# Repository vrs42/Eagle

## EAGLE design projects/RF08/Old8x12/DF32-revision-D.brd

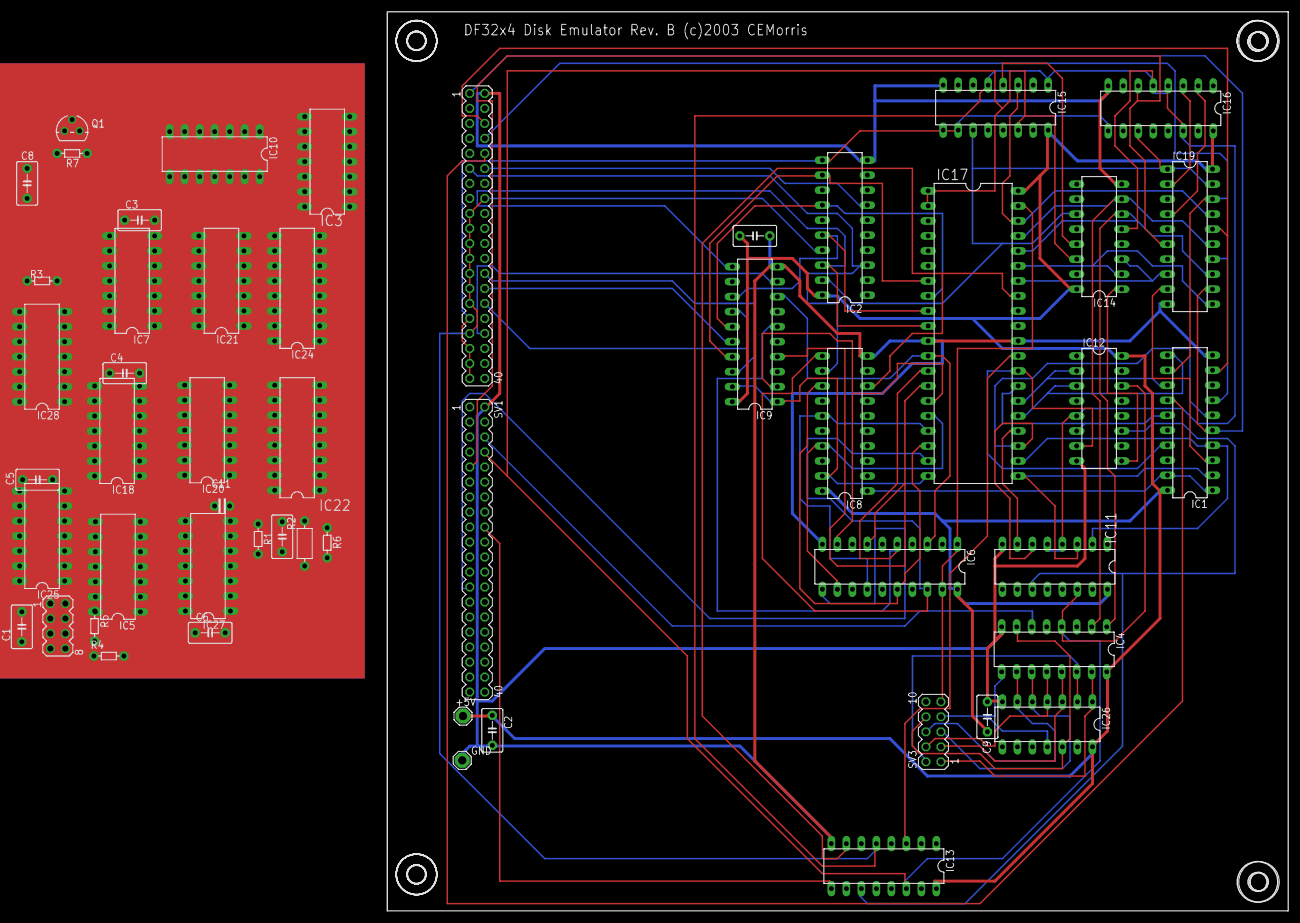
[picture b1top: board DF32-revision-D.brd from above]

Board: 2 copper layers, 152.5 x 152.2 mm, 56 parts (0 on the bottom side), 153 nets.

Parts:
+5V: SE14
C1, C2, C3, C4, C5, C6, C7, C8, C9, C10: C5B3.5
C11: C-2,5
GND: SE14
IC1, IC8, IC9, IC19: 74LS240N; DIL20
IC2, IC6: 74LS244N; DIL20
IC3: 74LS00N; DIL14
IC4: 74LS138N; DIL16
IC5: 74LS32N; DIL14
IC7, IC18, IC25: 74LS74N; DIL14
IC10: 74LS04N; DIL14
IC11, IC12, IC13, IC14, IC15, IC16: 74LS191N; DIL16
IC17: DS1258; DIL40
IC20: 74LS02N; DIL14
IC21: 74LS01N; DIL14
IC22, IC24: 74LS155N; DIL16
IC26: 74LS30N; DIL14
IC27: 74LS86N; DIL14
IC28: 74LS07N; DIL14
Q1: 2N3904; TO92
R1: 1K; R-5
R2: 1K; R-7,5
R3, R4, R5: 220; R-5
R6: 0; R-5
R7: 4.7K; R-5
SV1: BUS1; MA20-2
SV2: BUS2; MA20-2
SV3: WRLOCK; MA05-2
SV4: PANEL LEDS; MA04-2
U$1, U$2, U$3, U$4: 3,0

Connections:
0V: IC2.17, IC7.2, IC7.12, IC11.4, IC11.5, IC12.5, IC13.5, IC14.5, IC15.1, IC15.5, IC16.4, IC16.5, IC16.14, R6.1, SV2.16, SV2.17, SV2.19, SV2.21, SV2.23, SV2.25, SV2.27, SV2.29, SV2.33
!660-663: IC5.8, IC22.2, IC24.2, IC24.14
!(NED+EWL): IC2.13, IC20.1
!ACBUS0: IC2.3, IC8.12, SV2.11
!ACBUS1: IC8.14, IC19.3, SV2.9
!ACBUS2: IC8.16, IC19.5, SV2.7
!ACBUS3: IC8.18, IC19.7, SV2.5
!ACBUS4: IC1.3, IC19.9, SV2.3
!ACBUS5: IC1.5, IC19.12, SV2.1
!ACBUS6: IC1.7, IC19.14, SV2.4
!ACBUS7: IC1.9, IC19.16, SV2.6
!ACBUS8: IC1.12, IC19.18, SV2.8
!ACBUS9: IC1.14, IC2.5, SV2.10
!ACBUS10: IC1.16, IC2.7, SV2.12
!ACBUS11: IC1.18, IC2.9, SV2.14
!ACCLEAR: IC21.1, IC28.4, IC28.6, IC28.8, IC28.12, SV1.1
!BADDAC: IC7.3, SV1.10
!BBREAK: IC4.4, IC10.13, IC11.14, IC12.14, IC13.14, IC14.14, IC15.14, IC17.1, IC17.2, SV1.8
!BRK_RQ: IC7.8, SV2.15
!BWCO: IC7.11, IC18.3, SV1.12
!DATA0: IC8.9, SV2.18
!DATA1: IC8.7, SV2.20
!DATA2: IC8.5, SV2.22
!DATA3: IC8.3, SV2.24
!DATA4: IC9.18, SV2.26
!DATA5: IC9.16, SV2.28
!DATA6: IC9.14, SV2.30
!DATA7: IC9.12, SV2.32
!DATA8: IC9.9, SV2.34
!DATA9: IC9.7, SV2.36
!DATA10: IC9.5, SV2.38
!DATA11: IC9.3, SV2.40
!DRL: IC2.15, IC7.6
!EA: IC10.10, SV1.4
!EWL: IC18.8, IC28.11
!INT_RQ: IC21.13, SV1.16
!IOP4: IC10.4, IC24.15
!IOS: IC21.4, IC21.10, IC28.2, SV1.14
!IOT601: IC22.7, IC27.12
!IOT602: IC3.12, IC24.7, IC25.3, IC28.3
!IOT604: IC3.13, IC7.4, IC24.9, IC25.1, IC28.9
!IOT612: IC24.6, IC28.1, IC28.5, IC28.13
!IOT614: IC2.19, IC14.11, IC15.11, IC16.11, IC19.1, IC19.19, IC24.10
!IOT621: IC10.5, IC22.5
!IOT622: IC10.9, IC20.11, IC24.5
!IOT624: IC1.1, IC1.19, IC8.1, IC24.11
!LAD: IC3.8, IC7.10, IC11.11, IC12.11, IC13.11
!OE: IC3.6, IC8.19, IC9.1, IC9.19, IC17.20
!SCL: IC7.1, IC7.13, IC18.1, IC18.13, IC20.10, IC25.13
!WE: IC2.1, IC6.1, IC6.19, IC17.39, IC27.9, R2.2, SV3.9
!WR1: IC4.15, IC26.1, SV3.1
!WR2: IC4.14, IC26.2, SV3.2
!WR3: IC4.13, IC26.3, SV3.3
!WR4: IC4.12, IC26.4, SV3.4
!WR5: IC4.11, IC26.5, SV3.5
!WR6: IC4.10, IC26.6, SV3.6
!WR7: IC4.9, IC26.11, SV3.7
!WR8: IC4.7, IC26.12, SV3.8
BAC0: IC13.9, SV1.18
BAC1: IC13.10, IC15.15, SV1.20
BAC2: IC13.1, IC14.9, SV1.22
BAC3: IC13.15, IC14.10, SV1.24
BAC4: IC12.9, IC14.1, SV1.26
BAC5: IC12.10, IC14.15, SV1.28
BAC6: IC12.1, IC16.10, SV1.30
BAC7: IC12.15, IC16.1, SV1.32
BAC8: IC11.9, IC16.15, SV1.34
BAC9: IC11.10, SV1.36
BAC10: IC11.1, SV1.38
BAC11: IC11.15, SV1.40
BIOP1: IC22.1, SV1.11
BIOP2: IC24.1, SV1.13
BIOP4: IC10.3, SV1.15
BMB0: IC6.2, SV1.17
BMB1: IC6.4, SV1.19
BMB2: IC6.6, SV1.21
BMB3: IC3.1, IC6.8, SV1.23
BMB4: IC3.2, IC6.11, SV1.25
BMB5: IC5.12, IC6.13, SV1.27
BMB6: IC5.13, IC6.15, SV1.29
BMB7: IC6.17, IC22.3, IC24.3, SV1.31
BMB8: IC2.2, IC22.13, IC24.13, SV1.33
BMB9: IC2.4, IC20.12, IC21.3, SV1.35
BMB10: IC2.6, SV1.37
BMB11: IC2.8, SV1.39
BRK_RQ: IC7.9, R7.2
BTS3: IC4.6, SV1.6
DATA_IN: IC3.4, IC4.5, IC25.5, SV2.13
DISK_LED: R4.1, SV4.3
DMA0: IC8.8, IC13.7, IC17.33
DMA1: IC8.6, IC13.6, IC17.32
DMA2: IC8.4, IC13.2, IC17.31
DMA3: IC8.2, IC13.3, IC17.29
DMA4: IC1.17, IC12.7, IC17.28
DMA5: IC1.15, IC12.6, IC17.27
DMA6: IC1.13, IC12.2, IC17.26
DMA7: IC1.11, IC12.3, IC17.25
DMA8: IC1.8, IC11.7, IC17.24
DMA9: IC1.6, IC11.6, IC17.23
DMA10: IC1.4, IC11.2, IC17.22
DMA11: IC1.2, IC11.3, IC17.21
DQ0: IC6.18, IC8.11, IC17.19
DQ1: IC6.16, IC8.13, IC17.18
DQ2: IC6.14, IC8.15, IC17.17
DQ3: IC6.12, IC8.17, IC17.16
DQ4: IC6.9, IC9.2, IC17.15
DQ5: IC6.7, IC9.4, IC17.14
DQ6: IC6.5, IC9.6, IC17.13
DQ7: IC6.3, IC9.8, IC17.12
DQ8: IC2.18, IC9.11, IC17.10
DQ9: IC2.16, IC9.13, IC17.9
DQ10: IC2.14, IC9.15, IC17.8
DQ11: IC2.12, IC9.17, IC17.7
DRL: IC5.2, IC7.5
EA1: IC10.11, IC16.3, IC19.2, SV1.5
EA2: IC16.2, IC19.4, SV1.7
EA3: IC16.6, IC19.6, SV1.9
EMA1: IC14.3, IC17.34, IC19.8
EMA2: IC14.2, IC17.35, IC19.11
EMA3: IC4.1, IC14.6, IC17.36, IC19.13
EMA4: IC4.2, IC14.7, IC17.37, IC19.15
EMA5: IC4.3, IC15.3, IC17.38, IC19.17
EWL: IC5.1, IC18.9, IC20.2
EWLSET: IC18.11, IC27.6
GND: C1.2, C2.2, C3.2, C4.2, C5.2, C6.2, C7.2, C8.2, C9.2, C10.2, C11.2, GND.MP, IC1.10, IC2.10, IC3.7, IC4.8, IC5.7, IC6.10, IC7.7, IC8.10, IC9.10, IC10.7, IC11.8, IC12.8, IC13.8, IC14.8, IC15.8, IC16.8, IC17.11, IC17.30, IC18.7, IC19.10, IC20.7, IC21.7, IC22.8, IC24.8, IC25.7, IC26.7, IC27.7, IC28.7, Q1.3, R6.2, SV1.2, SV2.2, SV4.5, SV4.7
IOT601: IC20.9, IC27.11
IOT621: IC10.6, IC21.9
LAD: IC3.9, IC3.10, IC3.11
unnamed: C11.1, IC27.5, IC27.8
unnamed: IC5.6, IC21.11, IC21.12
unnamed: IC28.10, R3.2
unnamed: IC3.5, IC10.12
unnamed: Q1.1, R4.2
unnamed: R5.2, SV4.6
unnamed: IC13.13, IC14.4
unnamed: IC12.13, IC13.4
unnamed: IC11.13, IC12.4
unnamed: IC3.3, IC5.9
unnamed: IC14.13, IC15.4
unnamed: IC5.10, IC5.11
unnamed: IC20.13, IC21.5
unnamed: IC5.3, IC20.5
unnamed: IC10.8, IC21.2
unnamed: IC26.8, IC27.4
unnamed: Q1.2, R7.1
NED: IC5.4, IC20.3, IC20.6, IC25.9
NEDSET: IC15.2, IC25.11
NOERR: IC20.4, IC21.8
PWRCLR: IC20.8, IC25.4, SV1.3
TRC: IC5.5, IC18.5, IC21.6
V+: IC2.11, IC15.9, IC15.10, IC16.9, IC18.2, IC18.4, IC18.10, IC18.12, IC22.14, IC22.15, IC25.2, IC25.10, IC25.12, IC27.1, IC27.2, IC27.10, IC27.13, R1.1, R2.1, SV2.31, SV2.35, SV2.37, SV2.39
VCC: +5V.MP, C1.1, C2.1, C3.1, C4.1, C5.1, C6.1, C7.1, C8.1, C9.1, C10.1, IC1.20, IC2.20, IC3.14, IC4.16, IC5.14, IC6.20, IC7.14, IC8.20, IC9.20, IC10.14, IC11.16, IC12.16, IC13.16, IC14.16, IC15.16, IC16.16, IC17.40, IC18.14, IC19.20, IC20.14, IC21.14, IC22.16, IC24.16, IC25.14, IC26.14, IC27.14, IC28.14, R1.2, R5.1, SV4.2, SV4.4, SV4.8
WRITELOCK_LED: R3.1, SV4.1

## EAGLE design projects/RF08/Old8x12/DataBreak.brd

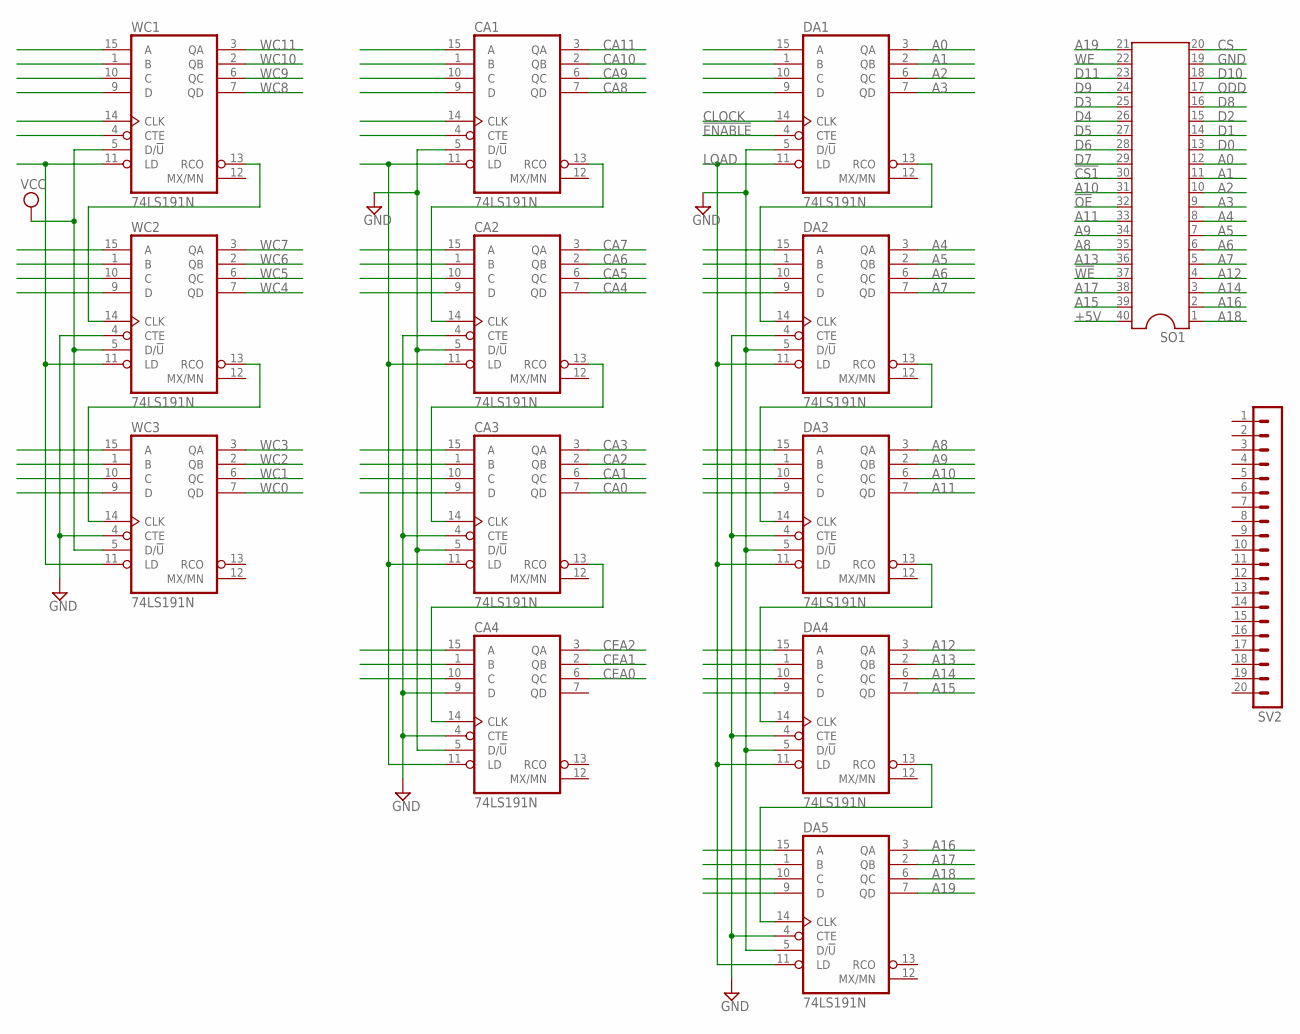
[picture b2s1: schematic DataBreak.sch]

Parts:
CA1, CA2, CA3, CA4: 74LS191N; DIL16
DA1, DA2, DA3, DA4, DA5: 74LS191N; DIL16
SO1: DIL40
SV2: MA20-1L
WC1, WC2, WC3: 74LS191N; DIL16

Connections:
!CS1: SO1.30
!ENABLE: DA1.4 (CTE)
!OE: SO1.32
!WE: SO1.37
+5V: SO1.40
A0: DA1.3 (QA), SO1.12
A1: DA1.2 (QB), SO1.11
A2: DA1.6 (QC), SO1.10
A3: DA1.7 (QD), SO1.9
A4: DA2.3 (QA), SO1.8
A5: DA2.2 (QB), SO1.7
A6: DA2.6 (QC), SO1.6
A7: DA2.7 (QD), SO1.5
A8: DA3.3 (QA), SO1.35
A9: DA3.2 (QB), SO1.34
A10: DA3.6 (QC), SO1.31
A11: DA3.7 (QD), SO1.33
A12: DA4.3 (QA), SO1.4
A13: DA4.2 (QB), SO1.36
A14: DA4.6 (QC), SO1.3
A15: DA4.7 (QD), SO1.39
A16: DA5.3 (QA), SO1.2
A17: DA5.2 (QB), SO1.38
A18: DA5.6 (QC), SO1.1
A19: DA5.7 (QD), SO1.21
CA0: CA3.7 (QD)
CA1: CA3.6 (QC)
CA2: CA3.2 (QB)
CA3: CA3.3 (QA)
CA4: CA2.7 (QD)
CA5: CA2.6 (QC)
CA6: CA2.2 (QB)
CA7: CA2.3 (QA)
CA8: CA1.7 (QD)
CA9: CA1.6 (QC)
CA10: CA1.2 (QB)
CA11: CA1.3 (QA)
CEA0: CA4.6 (QC)
CEA1: CA4.2 (QB)
CEA2: CA4.3 (QA)
CLOCK: DA1.14 (CLK)
CS: SO1.20
D0: SO1.13
D1: SO1.14
D2: SO1.15
D3: SO1.25
D4: SO1.26
D5: SO1.27
D6: SO1.28
D7: SO1.29
D8: SO1.16
D9: SO1.24
D10: SO1.18
D11: SO1.23
GND: CA1.5 (D/!U), CA1.8 (GND), CA2.4 (CTE), CA2.5 (D/!U), CA2.8 (GND), CA3.4 (CTE), CA3.5 (D/!U), CA3.8 (GND), CA4.4 (CTE), CA4.5 (D/!U), CA4.8 (GND), CA4.9 (D), DA1.5 (D/!U), DA1.8 (GND), DA2.4 (CTE), DA2.5 (D/!U), DA2.8 (GND), DA3.4 (CTE), DA3.5 (D/!U), DA3.8 (GND), DA4.4 (CTE), DA4.5 (D/!U), DA4.8 (GND), DA5.4 (CTE), DA5.5 (D/!U), DA5.8 (GND), SO1.19, WC1.8 (GND), WC2.4 (CTE), WC2.8 (GND), WC3.4 (CTE), WC3.8 (GND)
LOAD: DA1.11 (LD), DA2.11 (LD), DA3.11 (LD), DA4.11 (LD), DA5.11 (LD)
unnamed: DA1.13 (RCO), DA2.14 (CLK)
unnamed: DA2.13 (RCO), DA3.14 (CLK)
unnamed: DA3.13 (RCO), DA4.14 (CLK)
unnamed: DA4.13 (RCO), DA5.14 (CLK)
unnamed: WC1.13 (RCO), WC2.14 (CLK)
unnamed: WC2.13 (RCO), WC3.14 (CLK)
unnamed: CA1.13 (RCO), CA2.14 (CLK)
unnamed: CA2.13 (RCO), CA3.14 (CLK)
unnamed: CA3.13 (RCO), CA4.14 (CLK)
unnamed: CA1.11 (LD), CA2.11 (LD), CA3.11 (LD), CA4.11 (LD)
unnamed: WC1.11 (LD), WC2.11 (LD), WC3.11 (LD)
ODD: SO1.17
VCC: CA1.16 (VCC), CA2.16 (VCC), CA3.16 (VCC), CA4.16 (VCC), DA1.16 (VCC), DA2.16 (VCC), DA3.16 (VCC), DA4.16 (VCC), DA5.16 (VCC), WC1.5 (D/!U), WC1.16 (VCC), WC2.5 (D/!U), WC2.16 (VCC), WC3.5 (D/!U), WC3.16 (VCC)
WC0: WC3.7 (QD)
WC1: WC3.6 (QC)
WC2: WC3.2 (QB)
WC3: WC3.3 (QA)
WC4: WC2.7 (QD)
WC5: WC2.6 (QC)
WC6: WC2.2 (QB)
WC7: WC2.3 (QA)
WC8: WC1.7 (QD)
WC9: WC1.6 (QC)
WC10: WC1.2 (QB)
WC11: WC1.3 (QA)
WE: SO1.22

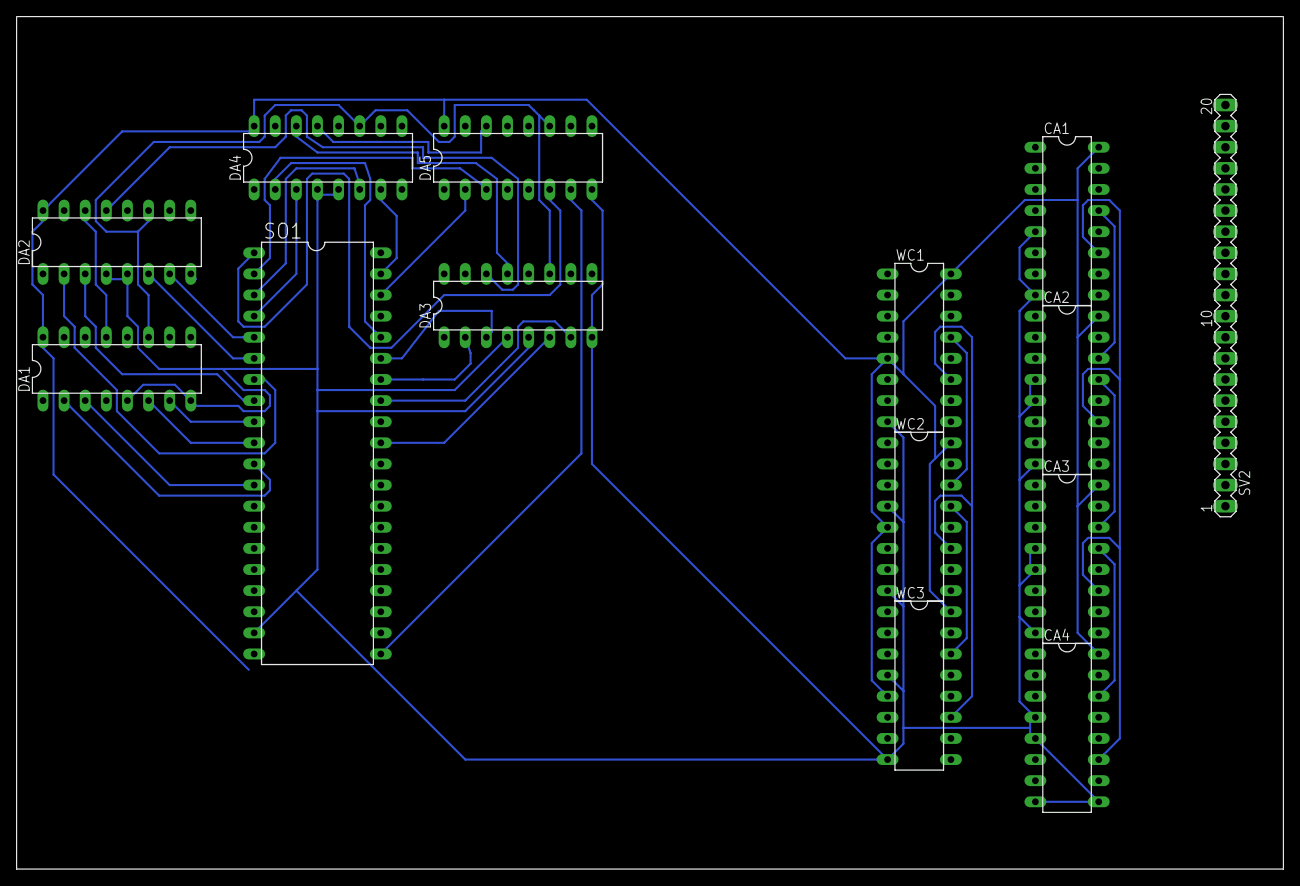
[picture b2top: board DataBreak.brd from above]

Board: 2 copper layers, 152.4 x 102.5 mm, 14 parts (0 on the bottom side), 34 nets.

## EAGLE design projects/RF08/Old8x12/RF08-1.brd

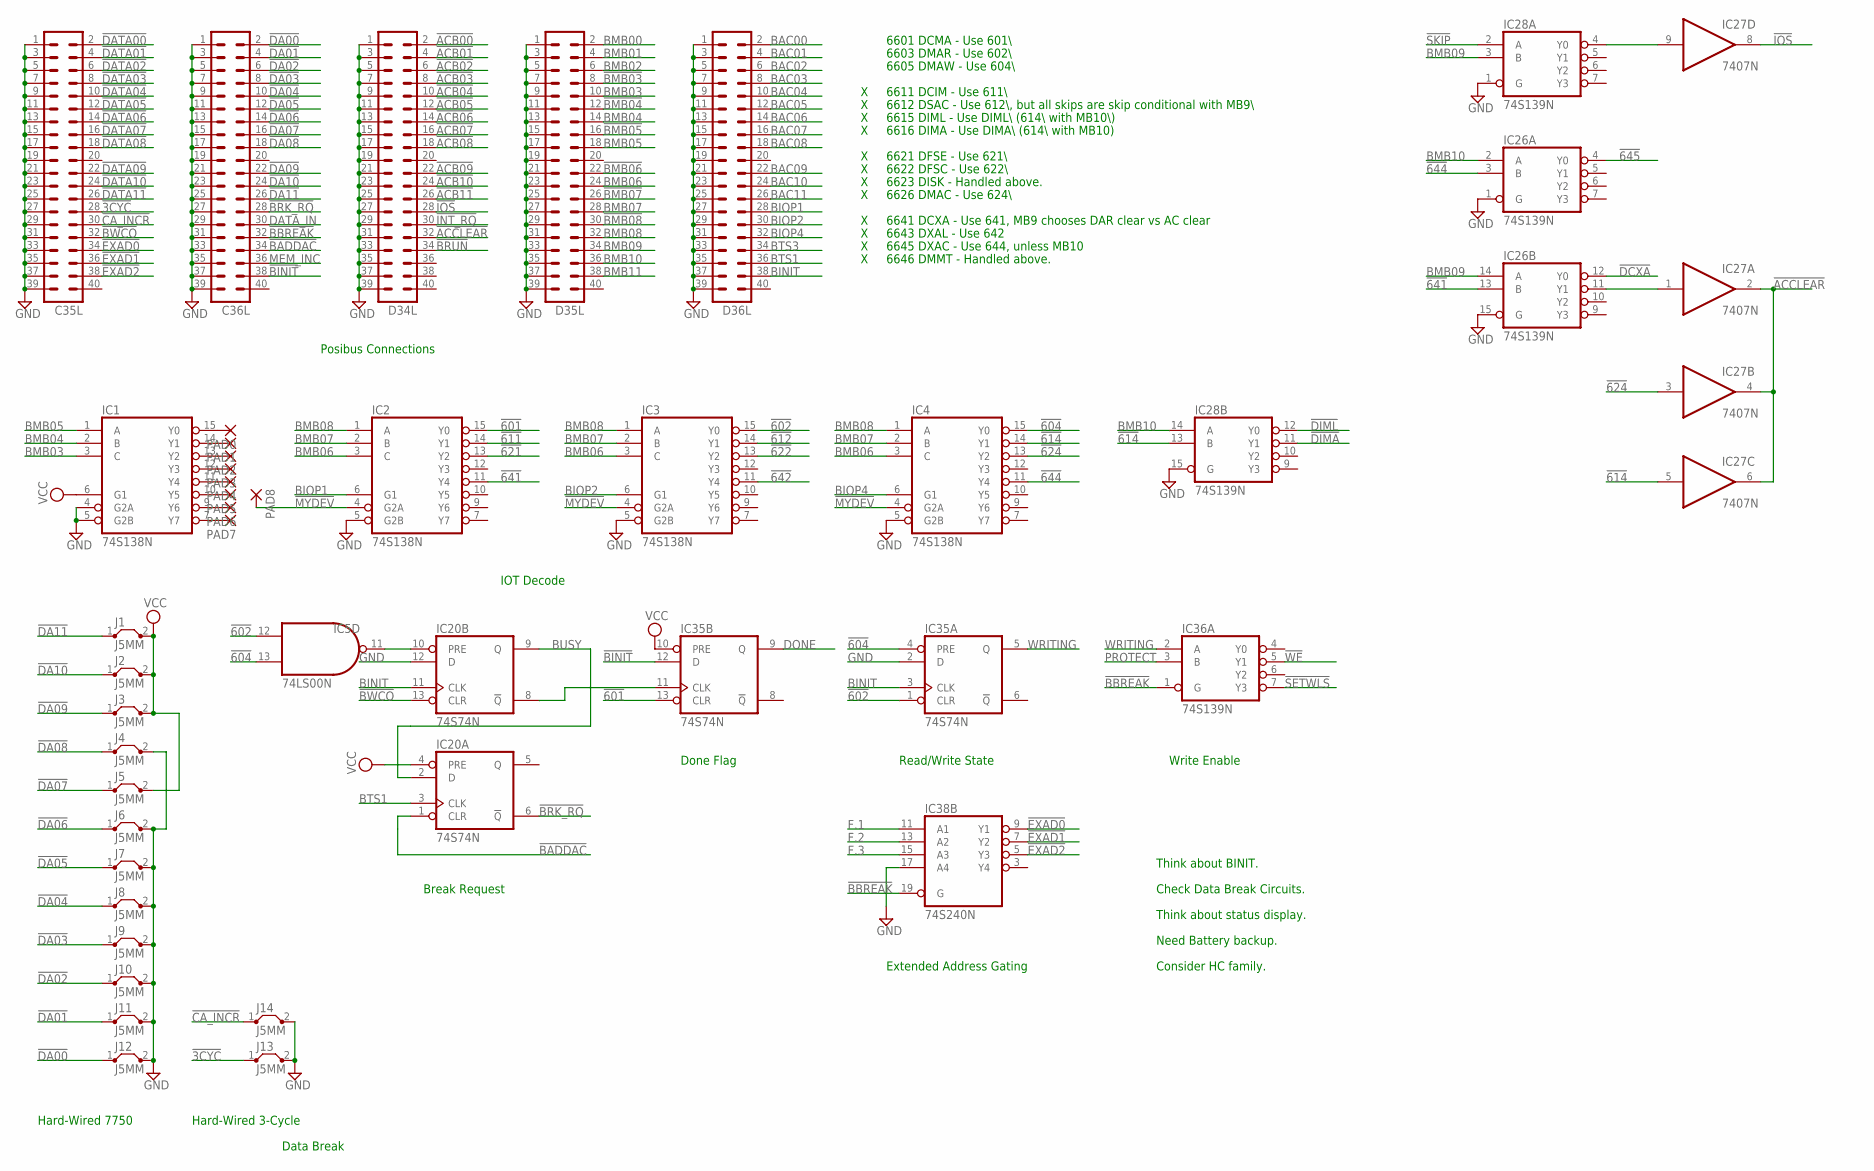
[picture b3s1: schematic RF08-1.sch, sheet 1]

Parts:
C35L, C36L: MA20-2
D34L, D35L, D36L: MA20-2
IC1, IC2, IC3, IC4: 74S138N; DIL16
IC5: 74LS00N; DIL14
IC20, IC35: 74S74N; DIL14
IC26, IC28, IC36: 74S139N; DIL16
IC27: 7407N; DIL14
IC38: 74S240N; DIL20
J1, J2, J3, J4, J5, J6, J7, J8, J9, J10, J11, J12, J13, J14: J5MM; 05
PAD0, PAD1, PAD2, PAD3, PAD4, PAD5, PAD6, PAD7, PAD8: 1,6/0,8

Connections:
!3CYC: C35L.28, J13.1
!601: IC2.15 (Y0), IC35.13 (CLR); also elsewhere on the board
!602: IC3.15 (Y0), IC5.12 (I0), IC35.1 (CLR); also elsewhere on the board
!604: IC4.15 (Y0), IC5.13 (I1), IC35.4 (PRE); also elsewhere on the board
!611: IC2.14 (Y1); also elsewhere on the board
!612: IC3.14 (Y1); also elsewhere on the board
!614: IC4.14 (Y1), IC27.5 (I), IC28.13 (B)
!621: IC2.13 (Y2); also elsewhere on the board
!622: IC3.13 (Y2); also elsewhere on the board
!624: IC4.13 (Y2), IC27.3 (I); also elsewhere on the board
!641: IC2.11 (Y4), IC26.13 (B)
!642: IC3.11 (Y4); also elsewhere on the board
!644: IC4.11 (Y4), IC26.3 (B)
!645: IC26.4 (Y0); also elsewhere on the board
!ACB00: D34L.2; also elsewhere on the board
!ACB01: D34L.4; also elsewhere on the board
!ACB02: D34L.6; also elsewhere on the board
!ACB03: D34L.8; also elsewhere on the board
!ACB04: D34L.10; also elsewhere on the board
!ACB05: D34L.12; also elsewhere on the board
!ACB06: D34L.14; also elsewhere on the board
!ACB07: D34L.16; also elsewhere on the board
!ACB08: D34L.18; also elsewhere on the board
!ACB09: D34L.22; also elsewhere on the board
!ACB10: D34L.24; also elsewhere on the board
!ACB11: D34L.26; also elsewhere on the board
!ACCLEAR: D34L.32, IC27.2 (O), IC27.4 (O), IC27.6 (O)
!BADDAC: C36L.34, IC20.1 (CLR)
!BBREAK: C36L.32, IC36.1 (G), IC38.19 (G); also elsewhere on the board
!BINIT: C36L.38, IC35.12 (D)
!BMB03: D35L.8
!BMB04: D35L.12
!BMB05: D35L.16
!BMB06: D35L.22
!BMB07: D35L.26
!BMB08: D35L.30
!BRK_RQ: C36L.28, IC20.6 (!Q)
!BRUN: D34L.34
!BWCO: C35L.32, IC20.13 (CLR)
!CA_INCR: C35L.30, J14.1
!DA00: C36L.2, J12.1
!DA01: C36L.4, J11.1
!DA02: C36L.6, J10.1
!DA03: C36L.8, J9.1
!DA04: C36L.10, J8.1
!DA05: C36L.12, J7.1
!DA06: C36L.14, J6.1
!DA07: C36L.16, J5.1
!DA08: C36L.18, J4.1
!DA09: C36L.22, J3.1
!DA10: C36L.24, J2.1
!DA11: C36L.26, J1.1
!DATA00: C35L.2; also elsewhere on the board
!DATA01: C35L.4; also elsewhere on the board
!DATA02: C35L.6; also elsewhere on the board
!DATA03: C35L.8; also elsewhere on the board
!DATA04: C35L.10; also elsewhere on the board
!DATA05: C35L.12; also elsewhere on the board
!DATA06: C35L.14; also elsewhere on the board
!DATA07: C35L.16; also elsewhere on the board
!DATA08: C35L.18; also elsewhere on the board
!DATA09: C35L.22; also elsewhere on the board
!DATA10: C35L.24; also elsewhere on the board
!DATA11: C35L.26; also elsewhere on the board
!DCXA: IC26.12 (Y0); also elsewhere on the board
!DIMA: IC28.11 (Y1); also elsewhere on the board
!DIML: IC28.12 (Y0); also elsewhere on the board
!EXAD0: C35L.34, IC38.9 (Y1)
!EXAD1: C35L.36, IC38.7 (Y2)
!EXAD2: C35L.38, IC38.5 (Y3)
!INT_RQ: D34L.30; also elsewhere on the board
!IOS: D34L.28, IC27.8 (O)
!MYDEV: IC2.4 (G2A), IC3.4 (G2A), IC4.4 (G2A), PAD8.1
!SETWLS: IC36.7 (Y3); also elsewhere on the board
!SKIP: IC28.2 (A); also elsewhere on the board
!WE: IC36.5 (Y1); also elsewhere on the board
BAC00: D36L.2; also elsewhere on the board
BAC01: D36L.4; also elsewhere on the board
BAC02: D36L.6; also elsewhere on the board
BAC03: D36L.8; also elsewhere on the board
BAC04: D36L.10; also elsewhere on the board
BAC05: D36L.12; also elsewhere on the board
BAC06: D36L.14; also elsewhere on the board
BAC07: D36L.16; also elsewhere on the board
BAC08: D36L.18; also elsewhere on the board
BAC09: D36L.22; also elsewhere on the board
BAC10: D36L.24; also elsewhere on the board
BAC11: D36L.26; also elsewhere on the board
BINIT: D36L.38, IC20.11 (CLK), IC35.3 (CLK); also elsewhere on the board
BIOP1: D36L.28, IC2.6 (G1)
BIOP2: D36L.30, IC3.6 (G1)
BIOP4: D36L.32, IC4.6 (G1)
BMB00: D35L.2; also elsewhere on the board
BMB01: D35L.4; also elsewhere on the board
BMB02: D35L.6; also elsewhere on the board
BMB03: D35L.10, IC1.3 (C); also elsewhere on the board
BMB04: D35L.14, IC1.2 (B); also elsewhere on the board
BMB05: D35L.18, IC1.1 (A); also elsewhere on the board
BMB06: D35L.24, IC2.3 (C), IC3.3 (C), IC4.3 (C); also elsewhere on the board
BMB07: D35L.28, IC2.2 (B), IC3.2 (B), IC4.2 (B); also elsewhere on the board
BMB08: D35L.32, IC2.1 (A), IC3.1 (A), IC4.1 (A); also elsewhere on the board
BMB09: D35L.34, IC26.14 (A), IC28.3 (B); also elsewhere on the board
BMB10: D35L.36, IC26.2 (A), IC28.14 (A); also elsewhere on the board
BMB11: D35L.38; also elsewhere on the board
BTS1: D36L.36, IC20.3 (CLK)
BTS3: D36L.34
BUSY: IC20.2 (D), IC20.9 (Q); also elsewhere on the board
DATA_IN: C36L.30
DONE: IC35.9 (Q); also elsewhere on the board
F.1: IC38.11 (A1); also elsewhere on the board
F.2: IC38.13 (A2); also elsewhere on the board
F.3: IC38.15 (A3); also elsewhere on the board
GND: C35L.1, C35L.3, C35L.5, C35L.7, C35L.9, C35L.11, C35L.13, C35L.15, C35L.17, C35L.19, C35L.21, C35L.23, C35L.25, C35L.27, C35L.29, C35L.31, C35L.33, C35L.35, C35L.37, C35L.39, C36L.1, C36L.3, C36L.5, C36L.7, C36L.9, C36L.11, C36L.13, C36L.15, C36L.17, C36L.19, C36L.21, C36L.23, C36L.25, C36L.27, C36L.29, C36L.31, C36L.33, C36L.35, C36L.37, C36L.39, D34L.1, D34L.3, D34L.5, D34L.7, D34L.9, D34L.11, D34L.13, D34L.15, D34L.17, D34L.19, D34L.21, D34L.23, D34L.25, D34L.27, D34L.29, D34L.31, D34L.33, D34L.35, D34L.37, D34L.39, D35L.1, D35L.3, D35L.5, D35L.7, D35L.9, D35L.11, D35L.13, D35L.15, D35L.17, D35L.19, D35L.21, D35L.23, D35L.25, D35L.27, D35L.29, D35L.31, D35L.33, D35L.35, D35L.37, D35L.39, D36L.1, D36L.3, D36L.5, D36L.7, D36L.9, D36L.11, D36L.13, D36L.15, D36L.17, D36L.19, D36L.21, D36L.23, D36L.25, D36L.27, D36L.29, D36L.31, D36L.33, D36L.35, D36L.37, D36L.39, IC1.4 (G2A), IC1.5 (G2B), IC1.8 (GND), IC2.5 (G2B), IC2.8 (GND), IC3.5 (G2B), IC3.8 (GND), IC4.5 (G2B), IC4.8 (GND), IC5.7 (GND), IC20.7 (GND), IC20.12 (D), IC26.1 (G), IC26.8 (GND), IC26.15 (G), IC27.7 (GND), IC28.1 (G), IC28.8 (GND), IC28.15 (G), IC35.2 (D), IC35.7 (GND), IC36.8 (GND), IC38.10 (GND), IC38.17 (A4), J4.2, J6.2, J7.2, J8.2, J9.2, J10.2, J11.2, J12.2, J13.2, J14.2; also elsewhere on the board
MEM_INC: C36L.36
unnamed: IC1.9 (Y6), PAD6.1
unnamed: IC20.8 (!Q), IC35.11 (CLK)
unnamed: IC1.15 (Y0), PAD0.1
unnamed: IC1.14 (Y1), PAD1.1
unnamed: IC1.13 (Y2), PAD2.1
unnamed: IC1.12 (Y3), PAD3.1
unnamed: IC1.11 (Y4), PAD4.1
unnamed: IC1.10 (Y5), PAD5.1
unnamed: IC1.7 (Y7), PAD7.1
unnamed: IC26.11 (Y1), IC27.1 (I)
unnamed: IC27.9 (I), IC28.4 (Y0)
unnamed: IC5.11 (O), IC20.10 (PRE)
PROTECT: IC36.3 (B); also elsewhere on the board
VCC: IC1.6 (G1), IC1.16 (VCC), IC2.16 (VCC), IC3.16 (VCC), IC4.16 (VCC), IC5.14 (VCC), IC20.4 (PRE), IC20.14 (VCC), IC26.16 (VCC), IC27.14 (VCC), IC28.16 (VCC), IC35.10 (PRE), IC35.14 (VCC), IC36.16 (VCC), IC38.20 (VCC), J1.2, J2.2, J3.2, J5.2; also elsewhere on the board
WRITING: IC35.5 (Q), IC36.2 (A); also elsewhere on the board

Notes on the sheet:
6601 DCMA - Use 601\\
6603 DMAR - Use 602\\
6605 DMAW - Use 604\\
6611 DCIM - Use 611\\
6612 DSAC - Use 612\\, but all skips are skip conditional with MB9\\
6615 DIML - Use DIML\\ (614\\ with MB10\\)
6616 DIMA - Use DIMA\\ (614\\ with MB10)
6621 DFSE - Use 621\\
6622 DFSC - Use 622\\
6623 DISK - Handled above.
6626 DMAC - Use 624\\
6641 DCXA - Use 641, MB9 chooses DAR clear vs AC clear
6643 DXAL - Use 642
6645 DXAC - Use 644, unless MB10
6646 DMMT - Handled above.
Posibus Connections
IOT Decode
Data Break
Hard-Wired 7750
Hard-Wired 3-Cycle
Think about BINIT.
Think about status display.
Break Request
Need Battery backup.
Done Flag
Extended Address Gating
Read/Write State
Write Enable
Check Data Break Circuits.
Consider HC family.

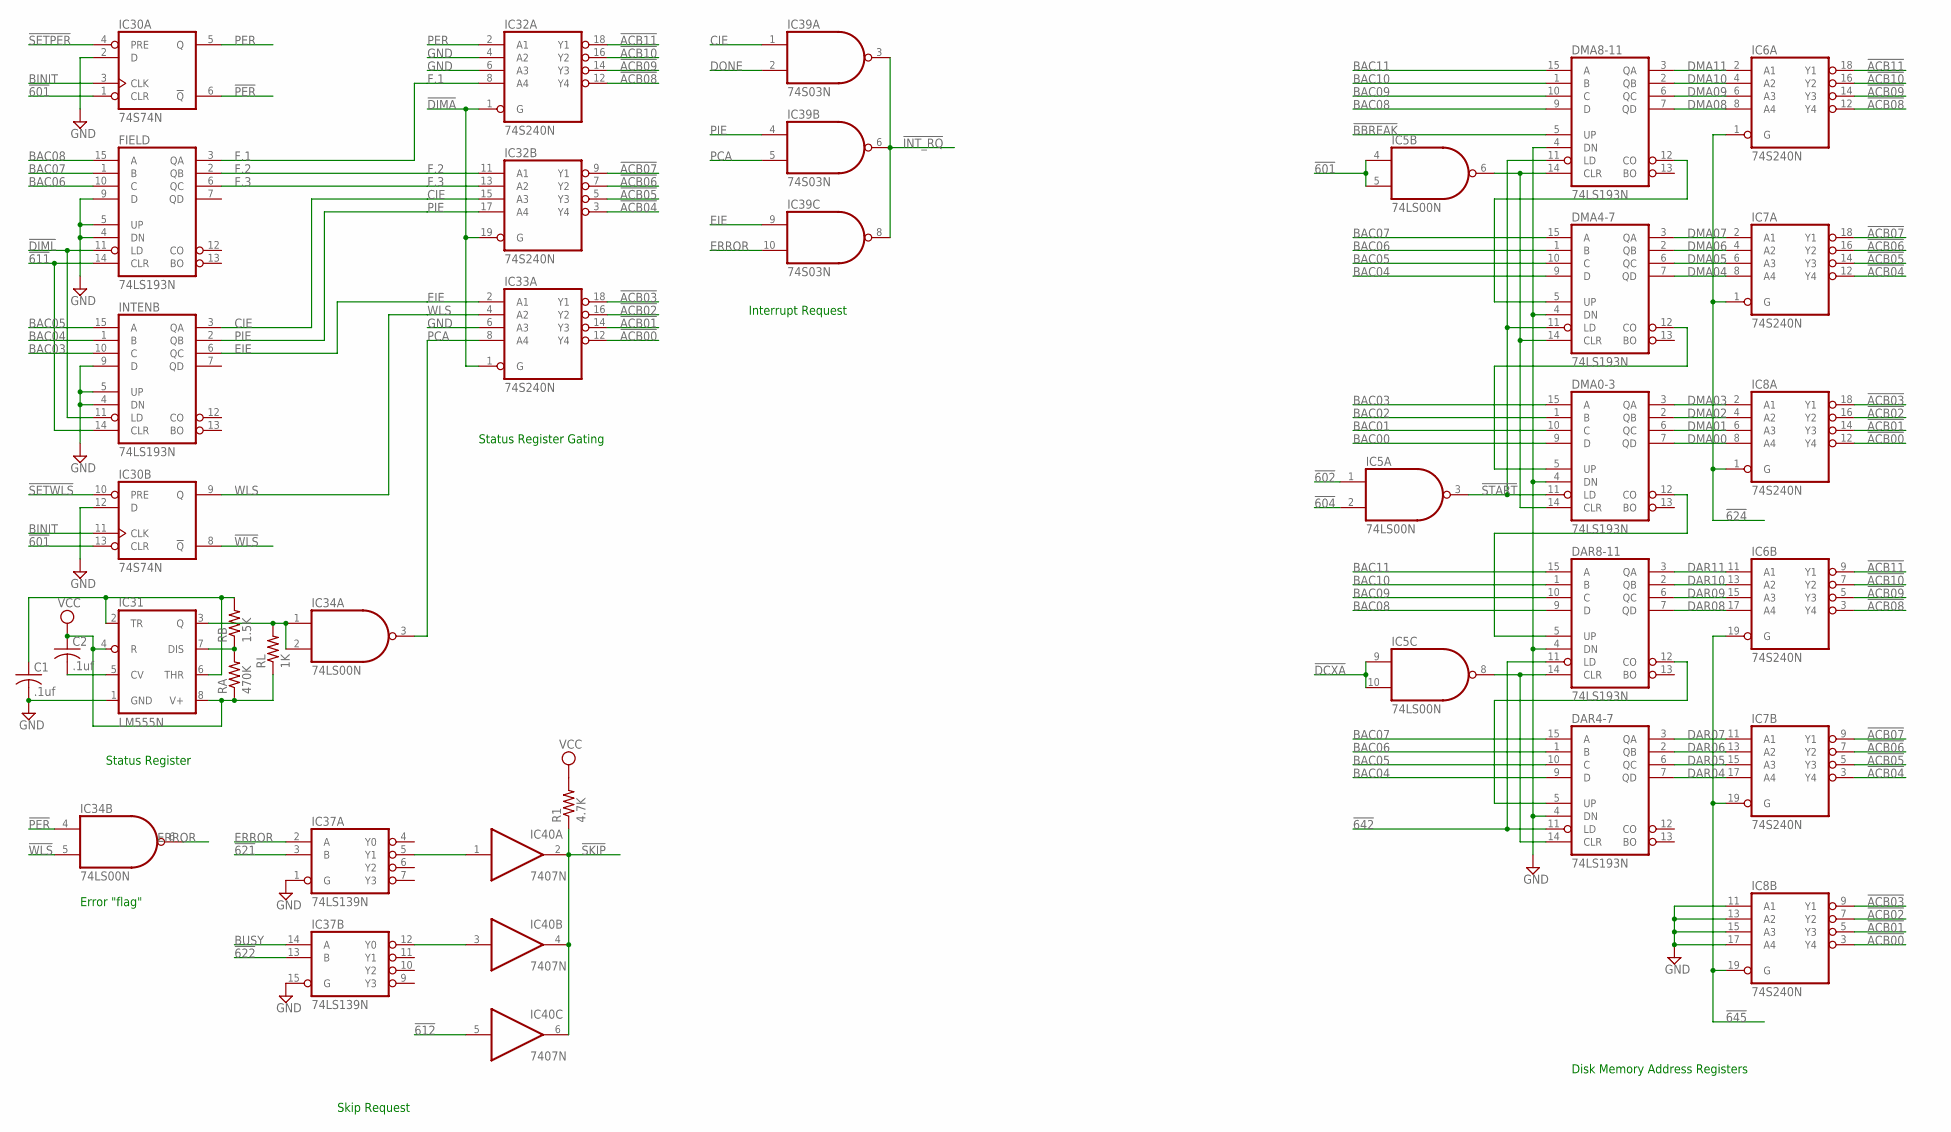
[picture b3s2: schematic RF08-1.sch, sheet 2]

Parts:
C1, C2: .1uf; C050-025X075
DAR4-7, DAR8-11: 74LS193N; DIL16
DMA0-3, DMA4-7, DMA8-11: 74LS193N; DIL16
FIELD: 74LS193N; DIL16
IC5, IC34: 74LS00N; DIL14
IC6, IC7, IC8, IC32, IC33: 74S240N; DIL20
IC30: 74S74N; DIL14
IC31: LM555N; DIL08
IC37: 74LS139N; DIL16
IC39: 74S03N; DIL14
IC40: 7407N; DIL14
INTENB: 74LS193N; DIL16
R1: 4.7K; 0207/10
RA: 470K; 0207/10
RB: 1.5K; 0207/10
RL: 1K; 0207/10

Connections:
!601: IC5.4 (I0), IC5.5 (I1), IC30.1 (CLR), IC30.13 (CLR); also elsewhere on the board
!602: IC5.1 (I0); also elsewhere on the board
!604: IC5.2 (I1); also elsewhere on the board
!611: FIELD.14 (CLR), INTENB.14 (CLR); also elsewhere on the board
!612: IC40.5 (I); also elsewhere on the board
!621: IC37.3 (B); also elsewhere on the board
!622: IC37.13 (B); also elsewhere on the board
!624: IC6.1 (G), IC7.1 (G), IC8.1 (G); also elsewhere on the board
!642: DAR4-7.11 (LD), DAR8-11.11 (LD); also elsewhere on the board
!645: IC6.19 (G), IC7.19 (G), IC8.19 (G); also elsewhere on the board
!ACB00: IC8.3 (Y4), IC8.12 (Y4), IC33.12 (Y4); also elsewhere on the board
!ACB01: IC8.5 (Y3), IC8.14 (Y3), IC33.14 (Y3); also elsewhere on the board
!ACB02: IC8.7 (Y2), IC8.16 (Y2), IC33.16 (Y2); also elsewhere on the board
!ACB03: IC8.9 (Y1), IC8.18 (Y1), IC33.18 (Y1); also elsewhere on the board
!ACB04: IC7.3 (Y4), IC7.12 (Y4), IC32.3 (Y4); also elsewhere on the board
!ACB05: IC7.5 (Y3), IC7.14 (Y3), IC32.5 (Y3); also elsewhere on the board
!ACB06: IC7.7 (Y2), IC7.16 (Y2), IC32.7 (Y2); also elsewhere on the board
!ACB07: IC7.9 (Y1), IC7.18 (Y1), IC32.9 (Y1); also elsewhere on the board
!ACB08: IC6.3 (Y4), IC6.12 (Y4), IC32.12 (Y4); also elsewhere on the board
!ACB09: IC6.5 (Y3), IC6.14 (Y3), IC32.14 (Y3); also elsewhere on the board
!ACB10: IC6.7 (Y2), IC6.16 (Y2), IC32.16 (Y2); also elsewhere on the board
!ACB11: IC6.9 (Y1), IC6.18 (Y1), IC32.18 (Y1); also elsewhere on the board
!BBREAK: DMA8-11.5 (UP); also elsewhere on the board
!DCXA: IC5.9 (I0), IC5.10 (I1); also elsewhere on the board
!DIMA: IC32.1 (G), IC32.19 (G), IC33.1 (G); also elsewhere on the board
!DIML: FIELD.11 (LD), INTENB.11 (LD); also elsewhere on the board
!INT_RQ: IC39.3 (O), IC39.6 (O), IC39.8 (O); also elsewhere on the board
!PER: IC30.6 (!Q), IC34.4 (I0)
!SETPER: IC30.4 (PRE); also elsewhere on the board
!SETWLS: IC30.10 (PRE); also elsewhere on the board
!SKIP: IC40.2 (O), IC40.4 (O), IC40.6 (O), R1.1; also elsewhere on the board
!START: DMA0-3.11 (LD), DMA4-7.11 (LD), DMA8-11.11 (LD), IC5.3 (O)
!WLS: IC30.8 (!Q), IC34.5 (I1)
BAC00: DMA0-3.9 (D); also elsewhere on the board
BAC01: DMA0-3.10 (C); also elsewhere on the board
BAC02: DMA0-3.1 (B); also elsewhere on the board
BAC03: DMA0-3.15 (A), INTENB.10 (C); also elsewhere on the board
BAC04: DAR4-7.9 (D), DMA4-7.9 (D), INTENB.1 (B); also elsewhere on the board
BAC05: DAR4-7.10 (C), DMA4-7.10 (C), INTENB.15 (A); also elsewhere on the board
BAC06: DAR4-7.1 (B), DMA4-7.1 (B), FIELD.10 (C); also elsewhere on the board
BAC07: DAR4-7.15 (A), DMA4-7.15 (A), FIELD.1 (B); also elsewhere on the board
BAC08: DAR8-11.9 (D), DMA8-11.9 (D), FIELD.15 (A); also elsewhere on the board
BAC09: DAR8-11.10 (C), DMA8-11.10 (C); also elsewhere on the board
BAC10: DAR8-11.1 (B), DMA8-11.1 (B); also elsewhere on the board
BAC11: DAR8-11.15 (A), DMA8-11.15 (A); also elsewhere on the board
BINIT: IC30.3 (CLK), IC30.11 (CLK); also elsewhere on the board
BUSY: IC37.14 (A); also elsewhere on the board
CIE: IC32.15 (A3), IC39.1 (I0), INTENB.3 (QA)
DAR04: DAR4-7.7 (QD), IC7.17 (A4); also elsewhere on the board
DAR05: DAR4-7.6 (QC), IC7.15 (A3); also elsewhere on the board
DAR06: DAR4-7.2 (QB), IC7.13 (A2); also elsewhere on the board
DAR07: DAR4-7.3 (QA), IC7.11 (A1); also elsewhere on the board
DAR08: DAR8-11.7 (QD), IC6.17 (A4); also elsewhere on the board
DAR09: DAR8-11.6 (QC), IC6.15 (A3); also elsewhere on the board
DAR10: DAR8-11.2 (QB), IC6.13 (A2); also elsewhere on the board
DAR11: DAR8-11.3 (QA), IC6.11 (A1); also elsewhere on the board
DMA00: DMA0-3.7 (QD), IC8.8 (A4); also elsewhere on the board
DMA01: DMA0-3.6 (QC), IC8.6 (A3); also elsewhere on the board
DMA02: DMA0-3.2 (QB), IC8.4 (A2); also elsewhere on the board
DMA03: DMA0-3.3 (QA), IC8.2 (A1); also elsewhere on the board
DMA04: DMA4-7.7 (QD), IC7.8 (A4); also elsewhere on the board
DMA05: DMA4-7.6 (QC), IC7.6 (A3); also elsewhere on the board
DMA06: DMA4-7.2 (QB), IC7.4 (A2); also elsewhere on the board
DMA07: DMA4-7.3 (QA), IC7.2 (A1); also elsewhere on the board
DMA08: DMA8-11.7 (QD), IC6.8 (A4); also elsewhere on the board
DMA09: DMA8-11.6 (QC), IC6.6 (A3); also elsewhere on the board
DMA10: DMA8-11.2 (QB), IC6.4 (A2); also elsewhere on the board
DMA11: DMA8-11.3 (QA), IC6.2 (A1); also elsewhere on the board
DONE: IC39.2 (I1); also elsewhere on the board
EIE: IC33.2 (A1), IC39.9 (I0), INTENB.6 (QC)
ERROR: IC34.6 (O), IC37.2 (A), IC39.10 (I1)
F.1: FIELD.3 (QA), IC32.8 (A4); also elsewhere on the board
F.2: FIELD.2 (QB), IC32.11 (A1); also elsewhere on the board
F.3: FIELD.6 (QC), IC32.13 (A2); also elsewhere on the board
GND: C1.2, DAR4-7.4 (DN), DAR4-7.8 (GND), DAR8-11.4 (DN), DAR8-11.8 (GND), DMA0-3.4 (DN), DMA0-3.8 (GND), DMA4-7.4 (DN), DMA4-7.8 (GND), DMA8-11.4 (DN), DMA8-11.8 (GND), FIELD.4 (DN), FIELD.5 (UP), FIELD.8 (GND), FIELD.9 (D), IC5.7 (GND), IC6.10 (GND), IC7.10 (GND), IC8.10 (GND), IC8.11 (A1), IC8.13 (A2), IC8.15 (A3), IC8.17 (A4), IC30.2 (D), IC30.7 (GND), IC30.12 (D), IC31.1 (GND), IC32.4 (A2), IC32.6 (A3), IC32.10 (GND), IC33.6 (A3), IC33.10 (GND), IC34.7 (GND), IC37.1 (G), IC37.8 (GND), IC37.15 (G), IC39.7 (GND), IC40.7 (GND), INTENB.4 (DN), INTENB.5 (UP), INTENB.8 (GND), INTENB.9 (D); also elsewhere on the board
unnamed: DMA0-3.5 (UP), DMA4-7.12 (CO)
unnamed: DAR4-7.14 (CLR), DAR8-11.14 (CLR), IC5.8 (O)
unnamed: DMA4-7.5 (UP), DMA8-11.12 (CO)
unnamed: DAR8-11.5 (UP), DMA0-3.12 (CO)
unnamed: DMA0-3.14 (CLR), DMA4-7.14 (CLR), DMA8-11.14 (CLR), IC5.6 (O)
unnamed: DAR4-7.5 (UP), DAR8-11.12 (CO)
unnamed: IC37.5 (Y1), IC40.1 (I)
unnamed: IC31.7 (DIS), RA.2, RB.1
unnamed: IC31.3 (Q), IC34.1 (I0), IC34.2 (I1), RL.2
unnamed: C1.1, IC31.2 (TR), IC31.6 (THR), RB.2
unnamed: IC37.12 (Y0), IC40.3 (I)
unnamed: C2.2, IC31.5 (CV)
PCA: IC33.8 (A4), IC34.3 (O), IC39.5 (I1)
PER: IC30.5 (Q), IC32.2 (A1)
PIE: IC32.17 (A4), IC39.4 (I0), INTENB.2 (QB)
VCC: C2.1, DAR4-7.16 (VCC), DAR8-11.16 (VCC), DMA0-3.16 (VCC), DMA4-7.16 (VCC), DMA8-11.16 (VCC), FIELD.16 (VCC), IC5.14 (VCC), IC6.20 (VCC), IC7.20 (VCC), IC8.20 (VCC), IC30.14 (VCC), IC31.4 (R), IC31.8 (V+), IC32.20 (VCC), IC33.20 (VCC), IC34.14 (VCC), IC37.16 (VCC), IC39.14 (VCC), IC40.14 (VCC), INTENB.16 (VCC), R1.2, RA.1, RL.1; also elsewhere on the board
WLS: IC30.9 (Q), IC33.4 (A2)

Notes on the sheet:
Disk Memory Address Registers
Status Register
Status Register Gating
Interrupt Request
Error "flag"
Skip Request
